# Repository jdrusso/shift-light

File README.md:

# shift-light
This repository contains code for a Miata shift light,
using a generic WS2812 individually addressible LED strip and ATTiny85 microcontroller.

## CAD Files
The ```cad/``` directory contains files generated in KiCAD for the PCB layout.
The included Gerber files should be useful in manufacturing this (as-yet-untested) board.

## Circuit Design
Most of the circuitry here is just stepping the 12V tach signal down to 5V for
the microcontroller to read it.

<!-- The voltage regulator sees (12 volts - 5 volts) * 1A max, so is dissipating
around 7 watts. This will definitely require a heatsink. Assuming a max ambient
temp of around 50 degrees Celsius, we need a heatsink with a thermal resistance
of at least 1.4 degrees/Watt, or one that can dissipate about 7W -->

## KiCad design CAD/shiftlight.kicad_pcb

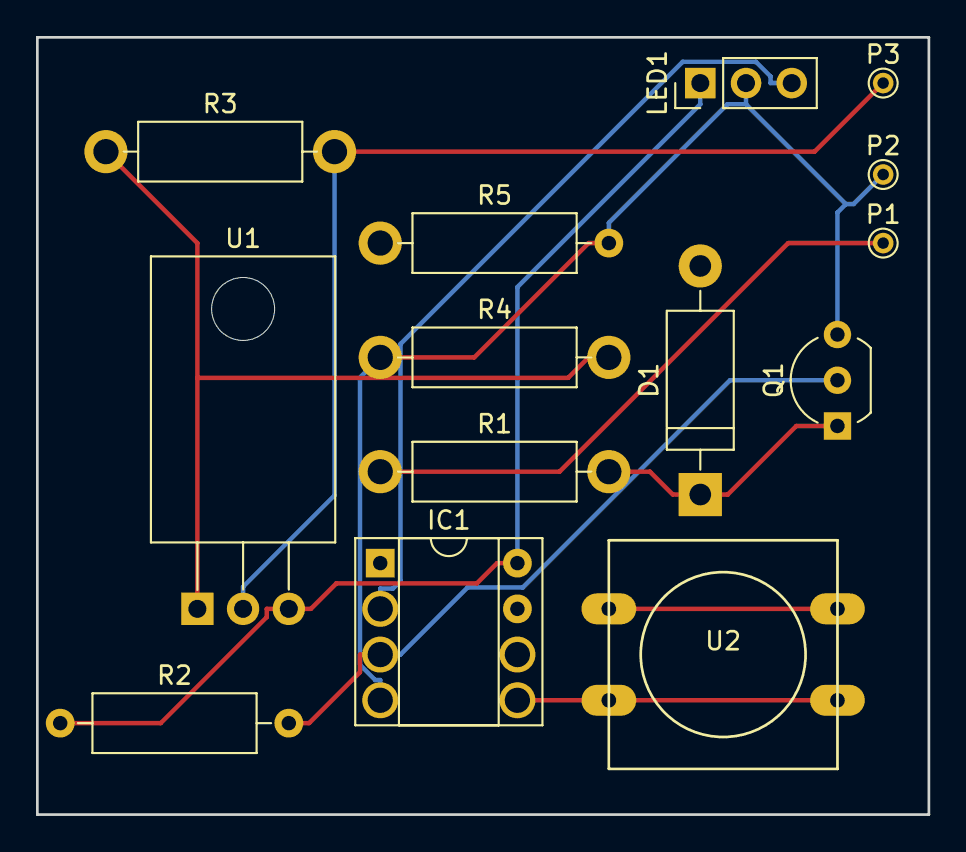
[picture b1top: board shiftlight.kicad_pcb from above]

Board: 2 copper layers, 49.5 x 43.2 mm, 14 parts (0 on the bottom side), 9 nets.

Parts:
D1: D; D_DO-15_P12.70mm_Horizontal
IC1: ATTINY85-P; DIP-8_W7.62mm_Socket
LED1: CONN_01X03; Pin_Header_Straight_1x03_Pitch2.54mm
P1, P2, P3: CONN_01X01; PINTST
Q1: Q_NPN_BCE; TO-92_Inline_Wide
R1: 3.3k; R_Axial_DIN0309_L9.0mm_D3.2mm_P12.70mm_Horizontal
R2, R5: 10k; R_Axial_DIN0309_L9.0mm_D3.2mm_P12.70mm_Horizontal
R3: 5; R_Axial_DIN0309_L9.0mm_D3.2mm_P12.70mm_Horizontal
R4: 7; R_Axial_DIN0309_L9.0mm_D3.2mm_P12.70mm_Horizontal
U1: LM317K; TO-220_Horizontal
U2: DG9421; SW_PUSH-12mm

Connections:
GND: IC1.4, LED1.2, P2.1, Q1.3, R4.1, R5.2
unnamed: D1.1, Q1.1, R1.2
unnamed: IC1.2, LED1.3
unnamed: IC1.3, Q1.2, R2.2
unnamed: IC1.5, U2.2
unnamed: IC1.8, LED1.1, R2.1, U1.3
unnamed: P1.1, R1.1
unnamed: P3.1, R3.2, U1.2
unnamed: R3.1, R4.2, U1.1

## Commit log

2017-02-15 Reorganized, added CAD files
2017-02-15 Re-added code
2017-02-28 Readme updated
2017-02-28 Rewritten with FastLED instead of Neopixel library
2017-03-03 Changed pin assignments for ATTiny85, and dimmed Night Mode brightness more.
2017-03-03 Made strobe function, cleaned up pixel display code
